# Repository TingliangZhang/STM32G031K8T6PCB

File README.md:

# STM32G031K8T6PCB
STM32G031K8T6 未来交互牌 开发板 PCB设计 KiCAD

参考设计：MB1455 [**NUCLEO-G031K8**](https://www.st.com/en/evaluation-tools/nucleo-g031k8.html) 原理图

## MCU

[STM32G031K8](https://www.st.com/en/microcontrollers-microprocessors/stm32g031k8.html)

## 晶振

晶振设计参考AN2867
$$
\mathrm{C}_{\mathrm{L}}=\frac{\mathrm{C}_{\mathrm{L} 1} \times \mathrm{C}_{\mathrm{L} 2}}{\mathrm{C}_{\mathrm{L} 1}+\mathrm{C}_{\mathrm{L} 2}}+\mathrm{C}_{\mathrm{S}}
$$
[ TST(台湾嘉硕) 32M ±10ppm 12pF ](https://item.szlcsc.com/510342.html)

求得负载电容为20pF

## 烧写器

[STLINK-V3MINI](https://www.st.com/en/development-tools/stlink-v3mini.html)

开发板上接口为STDC14 2x7 1.27mm排母

[ST-LINK/V2 ](https://www.st.com/en/development-tools/st-link-v2.html)

Target connection(SWD) 

20-pin JTAG 2x10 2.54mm 排针

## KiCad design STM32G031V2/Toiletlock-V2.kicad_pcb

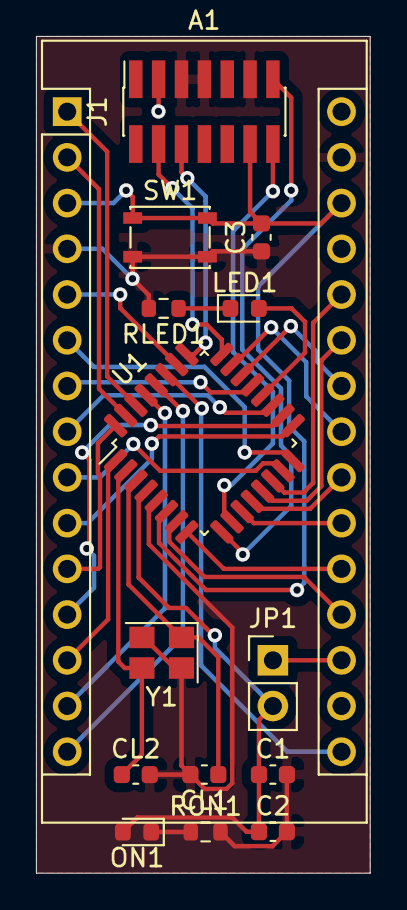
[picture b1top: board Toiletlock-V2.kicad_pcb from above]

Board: 2 copper layers, 18.5 x 46.5 mm, 15 parts (0 on the bottom side), 35 nets.

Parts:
A1: Arduino_Nano_v2.x; Arduino_Nano
C1: 4.7uF; C_0603_1608Metric
C2, C3: 100nF; C_0603_1608Metric
CL1, CL2: 20pF; C_0603_1608Metric
J1: Conn_ST_STDC14; PinSocket_2x07_P1.27mm_Vertical_SMD
JP1: Jumper; PinHeader_1x02_P2.54mm_Vertical
LED1: LED; LED_0603_1608Metric
ON1: LED; LED_0603_1608Metric
RLED1: 1k; R_0603_1608Metric
RON1: 1k; R_0603_1608Metric
SW1: SW_Push; SW_SPST_PTS810
U1: STM32G031K8T3; LQFP-32_7x7mm_P0.8mm
Y1: Crystal_GND24; Crystal_SMD_3225-4Pin_3.2x2.5mm

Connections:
+3V3: A1.17, C1.1, C2.1, J1.3, JP1.2, ON1.2, U1.4
/NRST: A1.3, A1.28, C3.2, J1.12, SW1.1, U1.6
/PA0: A1.19, U1.7
/PA1: A1.20, U1.8
/PA4: A1.21, U1.11
/PA5: A1.22, U1.12
/PA6: A1.25, U1.13
/PA7: A1.26, U1.14
/PA8: A1.12, U1.18
/PA9: A1.8, U1.19
/PA10: A1.7, U1.21
/PA11: A1.24, U1.22
/PA12: A1.23, U1.23
/PA15: A1.5, U1.26
/PB0: A1.9, U1.15
/PB1: A1.6, U1.16
/PB2: A1.10, U1.17
/PB3: A1.16, U1.27
/PB4: A1.15, U1.28
/PB5: A1.14, U1.29
/PB6: A1.1, U1.30
/PB7: A1.2, U1.31
/PB8: A1.11, U1.32
/PB9: A1.13, U1.1
/PC6: LED1.2, U1.20
/SWCLK: J1.6, U1.25
/SWDIO: J1.4, U1.24
GND: A1.4, A1.29, C1.2, C2.2, C3.1, CL1.2, CL2.2, J1.5, J1.7, J1.11, RLED1.2, RON1.2, SW1.2, U1.5, Y1.2, Y1.4
unnamed: A1.18, JP1.1
unnamed: CL1.1, U1.3, Y1.1
unnamed: CL2.1, U1.2, Y1.3
unnamed: LED1.1, RLED1.1
unnamed: ON1.1, RON1.1
T_VCP_RX: J1.14, U1.10
T_VCP_TX: J1.13, U1.9

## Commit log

2021-01-04 STM32G031K8T6PCB ini
2021-01-04 Simple system
2021-01-05 minimum
2021-01-07 Fab V1
2021-01-29 sym-lib
2021-01-29 Import From toilet lock V2
2021-01-29 add led on
2021-01-29 Finsh V2 Dev Board
